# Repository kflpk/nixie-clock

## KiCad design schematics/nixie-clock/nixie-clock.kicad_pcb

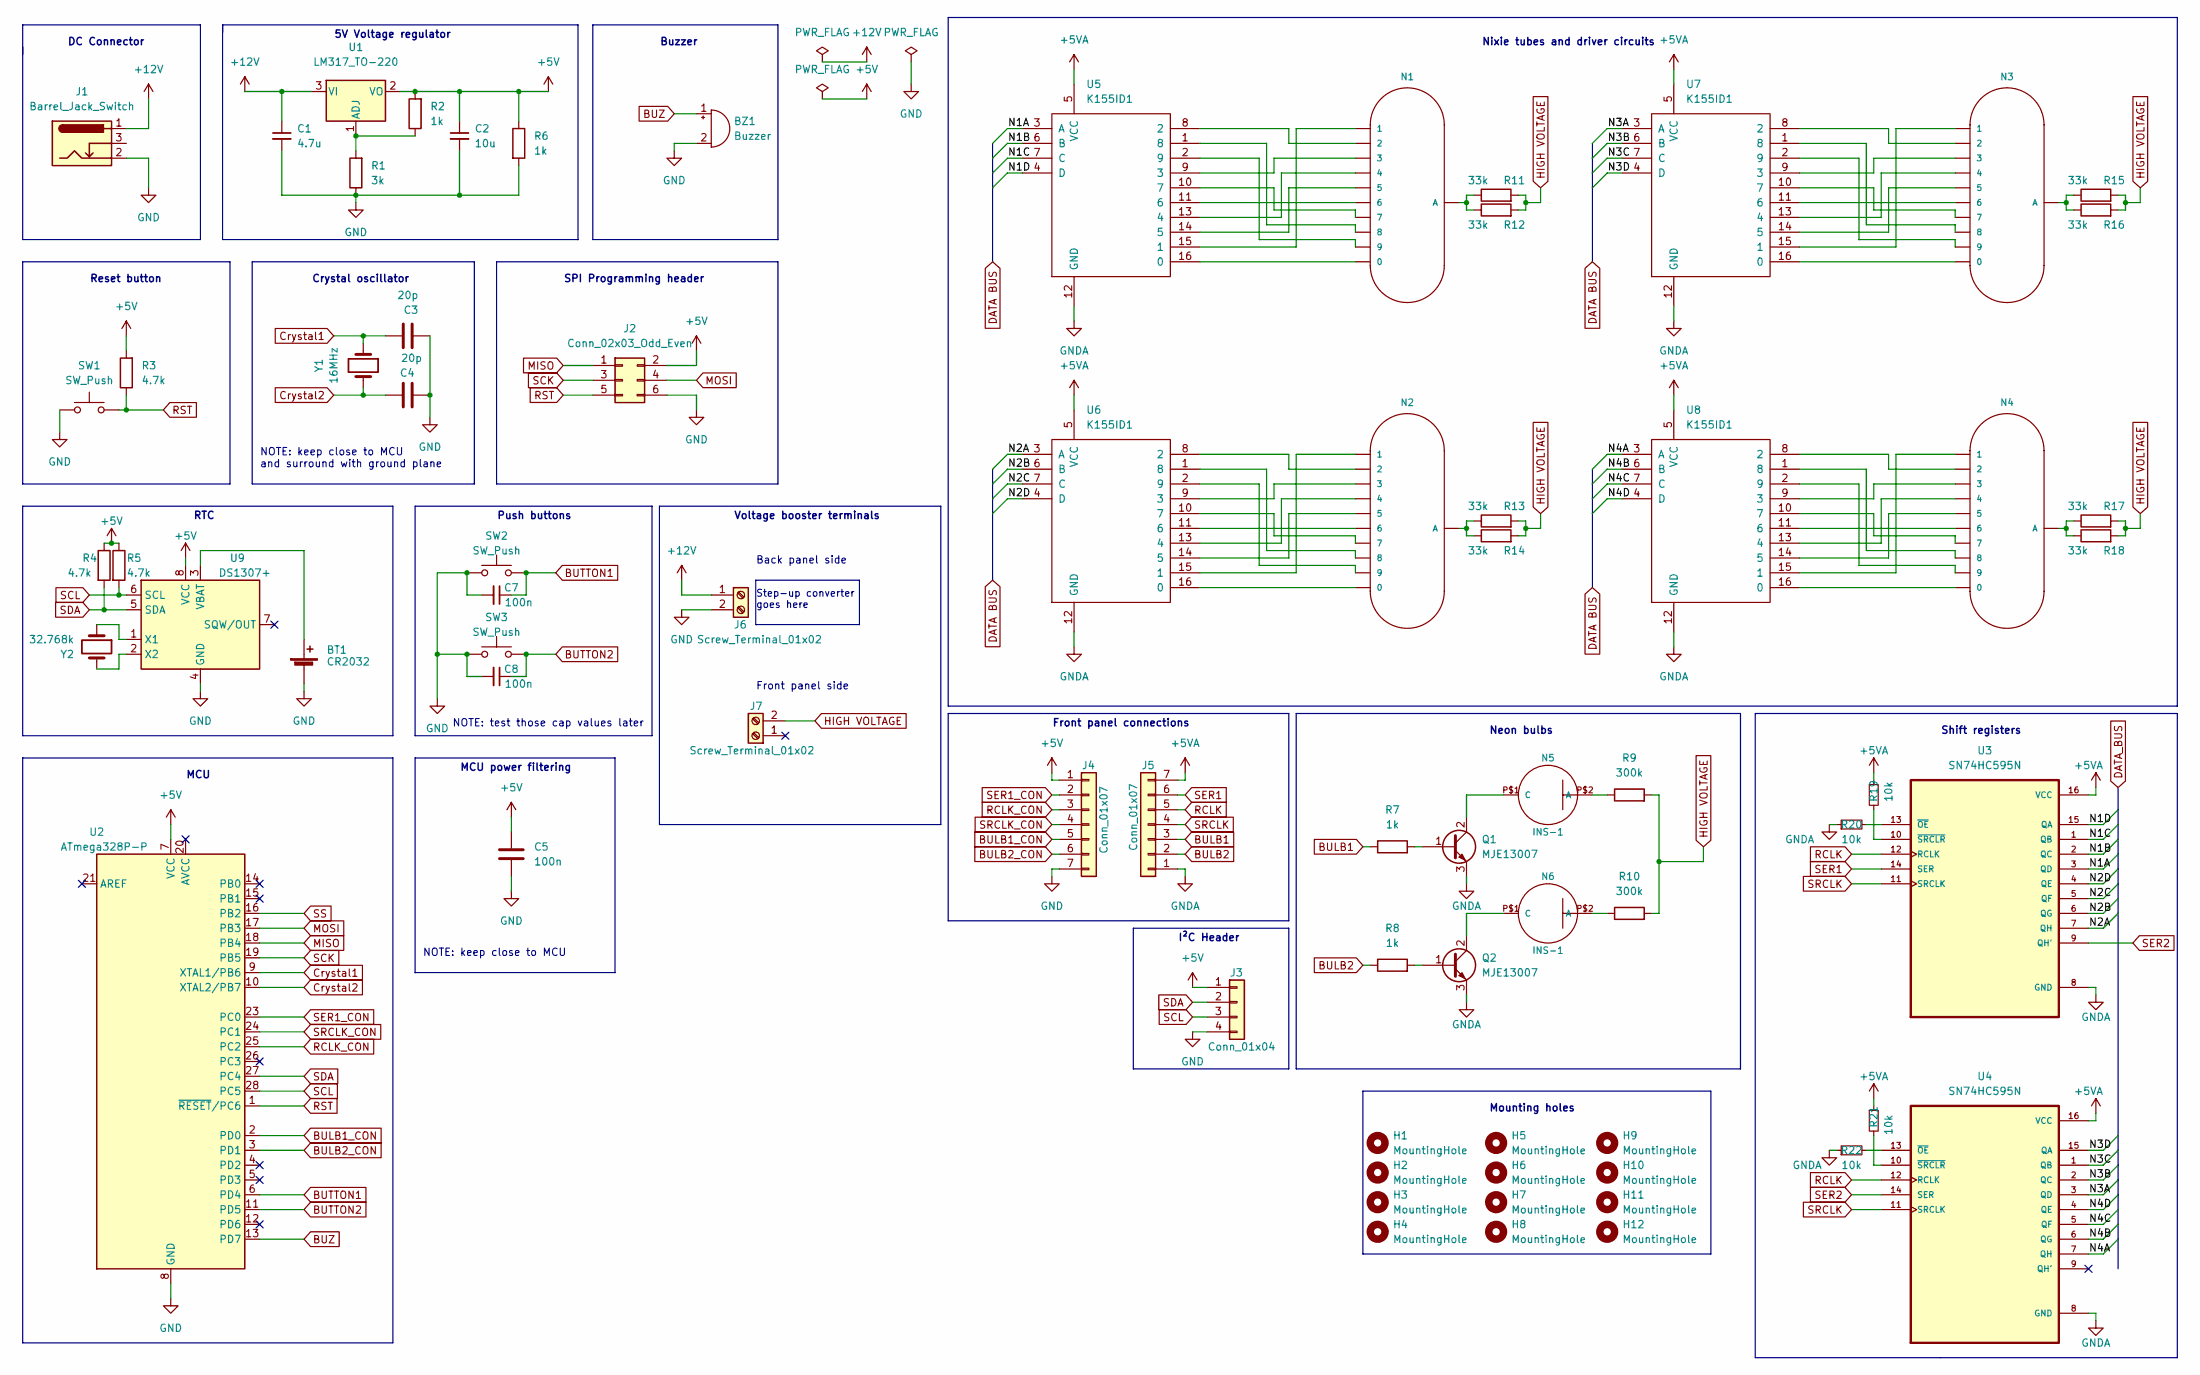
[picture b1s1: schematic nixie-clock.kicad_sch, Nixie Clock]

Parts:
BT1: CR2032; BatteryHolder_Keystone_1060_1x2032
BZ1: Buzzer; Buzzer_12x9.5RM7.6
C1: 4.7u; C_0805_2012Metric_Pad1.18x1.45mm_HandSolder
C2: 10u; C_0805_2012Metric_Pad1.18x1.45mm_HandSolder
C3, C4: 20p; C_0603_1608Metric_Pad1.08x0.95mm_HandSolder
C5, C7, C8: 100n; C_0805_2012Metric_Pad1.18x1.45mm_HandSolder
H1, H2, H3, H4, H5, H6, H7, H8, H9, H10, H11, H12: MountingHole; MountingHole_3mm
J1: Barrel_Jack_Switch; BarrelJack_Wuerth_6941xx301002
J2: Conn_02x03_Odd_Even; PinHeader_2x03_P2.54mm_Vertical
J3: Conn_01x04; PinHeader_1x04_P2.54mm_Vertical
J4, J5: Conn_01x07; PinHeader_1x07_P2.54mm_Horizontal
J6, J7: Screw_Terminal_01x02; TerminalBlock_Phoenix_MKDS-1,5-2_1x02_P5.00mm_Horizontal
N1, N2, N3, N4: IN-1
N5, N6: INS-1; mynixies-INS-1
Q1, Q2: MJE13007; TO-220-3_Vertical
R1: 3k; R_0805_2012Metric_Pad1.20x1.40mm_HandSolder
R2, R6, R7, R8: 1k; R_0805_2012Metric_Pad1.20x1.40mm_HandSolder
R3, R4, R5: 4.7k; R_0805_2012Metric_Pad1.20x1.40mm_HandSolder
R9, R10: 300k; R_0805_2012Metric_Pad1.20x1.40mm_HandSolder
R11, R12, R13, R14, R15, R16, R17, R18: 33k; R_1206_3216Metric_Pad1.30x1.75mm_HandSolder
R19, R20, R21, R22: 10k; R_0805_2012Metric_Pad1.20x1.40mm_HandSolder
SW1, SW2, SW3: SW_Push; SW_PUSH_6mm_H13mm
U1: LM317_TO-220; TO-220-3_Vertical
U2: ATmega328P-P; DIP-28_W7.62mm
U3, U4: SN74HC595N; DIP794W45P254L1969H508Q16
U5, U6, U7, U8: K155ID1; DIP-16_W7.62mm_Socket
U9: DS1307+; DIP-8_W7.62mm
Y1: 16MHz; Crystal_HC49-U_Vertical
Y2: 32.768k; Crystal_DS26_D2.0mm_L6.0mm_Horizontal

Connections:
+5V: C2.1, C5.1, J2.2, J3.1, J4.1, R2.2, R3.2, R4.1, R5.1, R6.1, U1.2 (VO), U2.7 (VCC), U9.8 (VCC)
+5VA: J5.7, R19.1, R21.1, U3.16 (VCC), U4.16 (VCC), U5.5 (VCC), U6.5 (VCC), U7.5 (VCC), U8.5 (VCC)
+12V: C1.1, J1.1, J6.1, U1.3 (VI)
/N1A: U3.3 (QD), U5.3 (A)
/N1B: U3.2 (QC), U5.6 (B)
/N1C: U3.1 (QB), U5.7 (C)
/N1D: U3.15 (QA), U5.4 (D)
/N2A: U3.7 (QH), U6.3 (A)
/N2B: U3.6 (QG), U6.6 (B)
/N2C: U3.5 (QF), U6.7 (C)
/N2D: U3.4 (QE), U6.4 (D)
/N3A: U4.3 (QD), U7.3 (A)
/N3B: U4.2 (QC), U7.6 (B)
/N3C: U4.1 (QB), U7.7 (C)
/N3D: U4.15 (QA), U7.4 (D)
/N4A: U4.7 (QH), U8.3 (A)
/N4B: U4.6 (QG), U8.6 (B)
/N4C: U4.5 (QF), U8.7 (C)
/N4D: U4.4 (QE), U8.4 (D)
BULB1: J5.3, R7.1
BULB1_CON: J4.5, U2.2 (PD0)
BULB2: J5.2, R8.1
BULB2_CON: J4.6, U2.3 (PD1)
BUTTON1: C7.1, SW2.2, U2.6 (PD4)
BUTTON2: C8.1, SW3.2, U2.11 (PD5)
BUZ: BZ1.1 (-), U2.13 (PD7)
Crystal1: C3.2, U2.9 (XTAL1/PB6), Y1.1
Crystal2: C4.2, U2.10 (XTAL2/PB7), Y1.2
GND: BT1.2 (-), BZ1.2 (+), C1.2, C2.2, C3.1, C4.1, C5.2, C7.2, C8.2, J1.2, J2.6, J3.4, J4.7, J6.2, R1.1, R6.2, SW1.1, SW2.1, SW3.1, U2.8 (GND), U2.22 (GND), U9.4 (GND)
GNDA: J5.1, Q1.3 (E), Q2.3 (E), R20.1, R22.1, U3.8 (GND), U4.8 (GND), U5.12 (GND), U6.12 (GND), U7.12 (GND), U8.12 (GND)
HIGH VOLTAGE: J7.2, R9.2, R10.2, R11.2, R12.2, R13.2, R14.2, R15.2, R16.2, R17.2, R18.2
MISO: J2.1, U2.18 (PB4)
MOSI: J2.4, U2.17 (PB3)
unnamed: BT1.1 (+), U9.3 (VBAT)
unnamed: N1.0, U5.16 (0)
unnamed: N1.1, U5.15 (1)
unnamed: N1.2, U5.8 (2)
unnamed: N1.3, U5.9 (3)
unnamed: N1.4, U5.13 (4)
unnamed: N1.5, U5.14 (5)
unnamed: N1.6, U5.11 (6)
unnamed: N1.7, U5.10 (7)
unnamed: N1.8, U5.1 (8)
unnamed: N1.9, U5.2 (9)
unnamed: N1.A, R11.1, R12.1
unnamed: N2.0, U6.16 (0)
unnamed: N2.1, U6.15 (1)
unnamed: N2.2, U6.8 (2)
unnamed: N2.3, U6.9 (3)
unnamed: N2.4, U6.13 (4)
unnamed: N2.5, U6.14 (5)
unnamed: N2.6, U6.11 (6)
unnamed: N2.7, U6.10 (7)
unnamed: N2.8, U6.1 (8)
unnamed: N2.9, U6.2 (9)
unnamed: N2.A, R13.1, R14.1
unnamed: N3.0, U7.16 (0)
unnamed: N3.1, U7.15 (1)
unnamed: N3.2, U7.8 (2)
unnamed: N3.3, U7.9 (3)
unnamed: N3.4, U7.13 (4)
unnamed: N3.5, U7.14 (5)
unnamed: N3.6, U7.11 (6)
unnamed: N3.7, U7.10 (7)
unnamed: N3.8, U7.1 (8)
unnamed: N3.9, U7.2 (9)
unnamed: N3.A, R15.1, R16.1
unnamed: N4.0, U8.16 (0)
unnamed: N4.1, U8.15 (1)
unnamed: N4.2, U8.8 (2)
unnamed: N4.3, U8.9 (3)
unnamed: N4.4, U8.13 (4)
unnamed: N4.5, U8.14 (5)
unnamed: N4.6, U8.11 (6)
unnamed: N4.7, U8.10 (7)
unnamed: N4.8, U8.1 (8)
unnamed: N4.9, U8.2 (9)
unnamed: N4.A, R17.1, R18.1
unnamed: N5.P$1 (C), Q1.2 (C)
unnamed: N5.P$2 (A), R9.1
unnamed: N6.P$1 (C), Q2.2 (C)
unnamed: N6.P$2 (A), R10.1
unnamed: Q1.1 (B), R7.2
unnamed: Q2.1 (B), R8.2
unnamed: R1.2, R2.1, U1.1 (ADJ)
unnamed: R19.2, U3.10 (~SRCLR)
unnamed: R20.2, U3.13 (~OE)
unnamed: R21.2, U4.10 (~SRCLR)
unnamed: R22.2, U4.13 (~OE)
unnamed: U9.1 (X1), Y2.1
unnamed: U9.2 (X2), Y2.2
RCLK: J5.5, U3.12 (RCLK), U4.12 (RCLK)
RCLK_CON: J4.3, U2.25 (PC2)
RST: J2.5, R3.1, SW1.2, U2.1 (~RESET/PC6)
SCK: J2.3, U2.19 (PB5)
SCL: J3.3, R5.2, U2.28 (PC5), U9.6 (SCL)
SDA: J3.2, R4.2, U2.27 (PC4), U9.5 (SDA)
SER1: J5.6, U3.14 (SER)
SER1_CON: J4.2, U2.23 (PC0)
SER2: U3.9 (QH'), U4.14 (SER)
SRCLK: J5.4, U3.11 (SRCLK), U4.11 (SRCLK)
SRCLK_CON: J4.4, U2.24 (PC1)
SS: U2.16 (PB2)

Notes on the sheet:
Step-up converter goes here
DC Connector
Nixie tubes and driver circuits
I²C Header
SPI Programming header
MCU power filtering
NOTE: keep close to MCU
Crystal oscillator
MCU
NOTE: test those cap values later
5V Voltage regulator
Buzzer
Front panel connections
Front panel side
RTC
Push buttons
Voltage booster terminals
Back panel side
NOTE: keep close to MCU and surround with ground plane
Neon bulbs
Shift registers
Reset button
Mounting holes

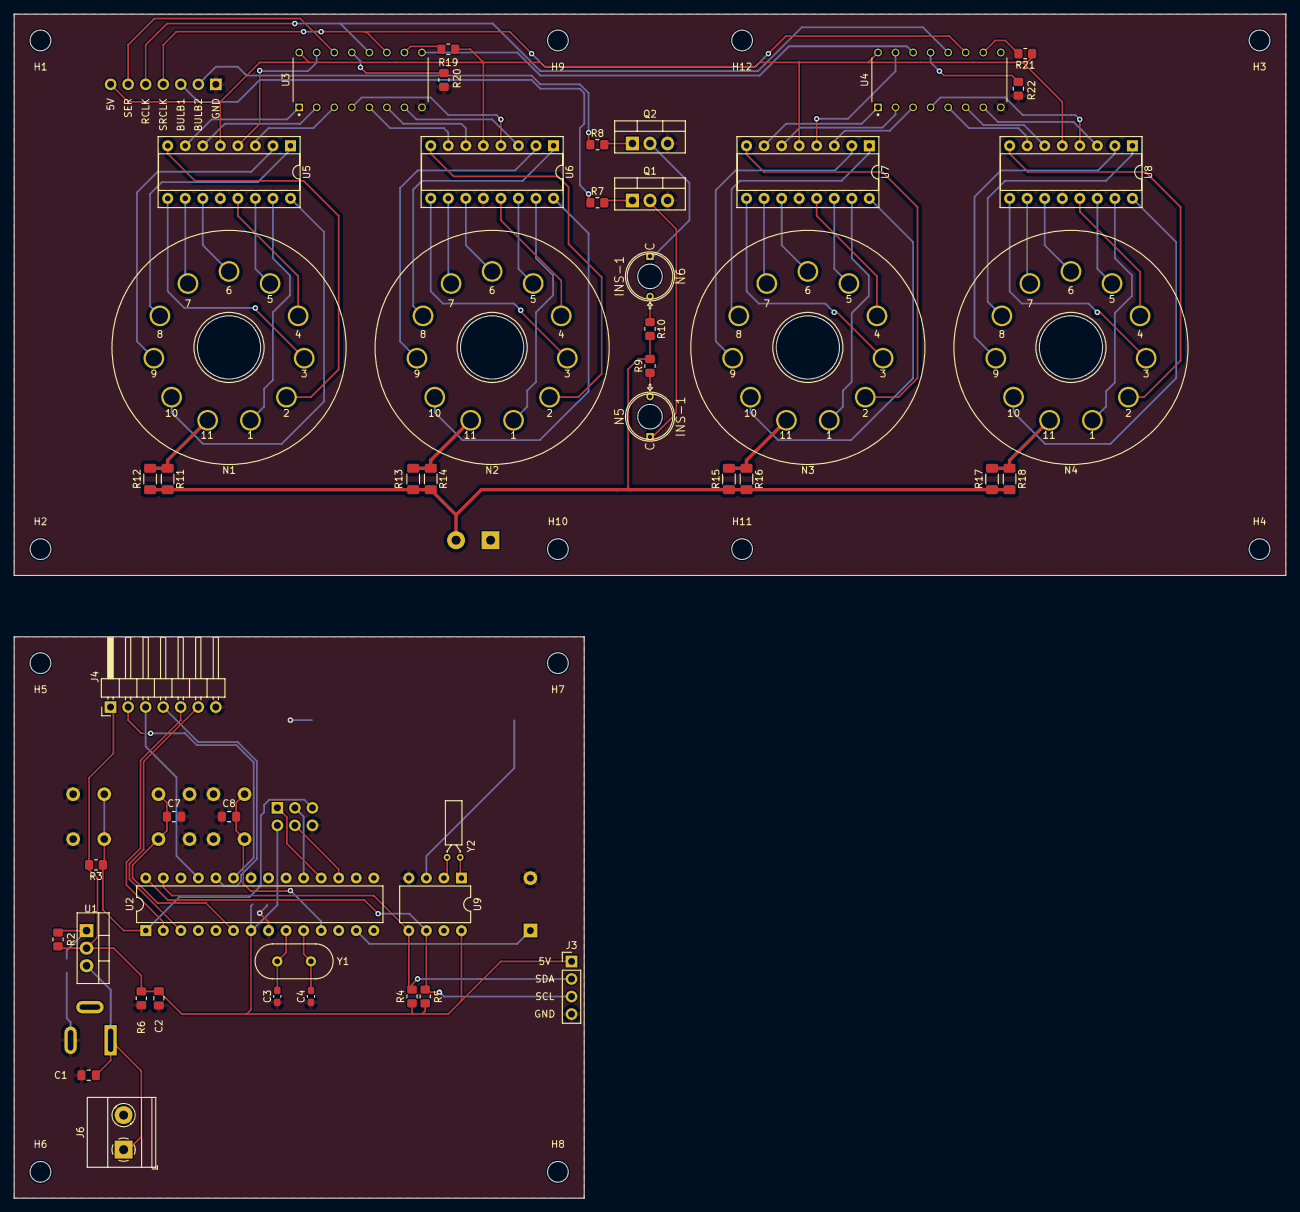
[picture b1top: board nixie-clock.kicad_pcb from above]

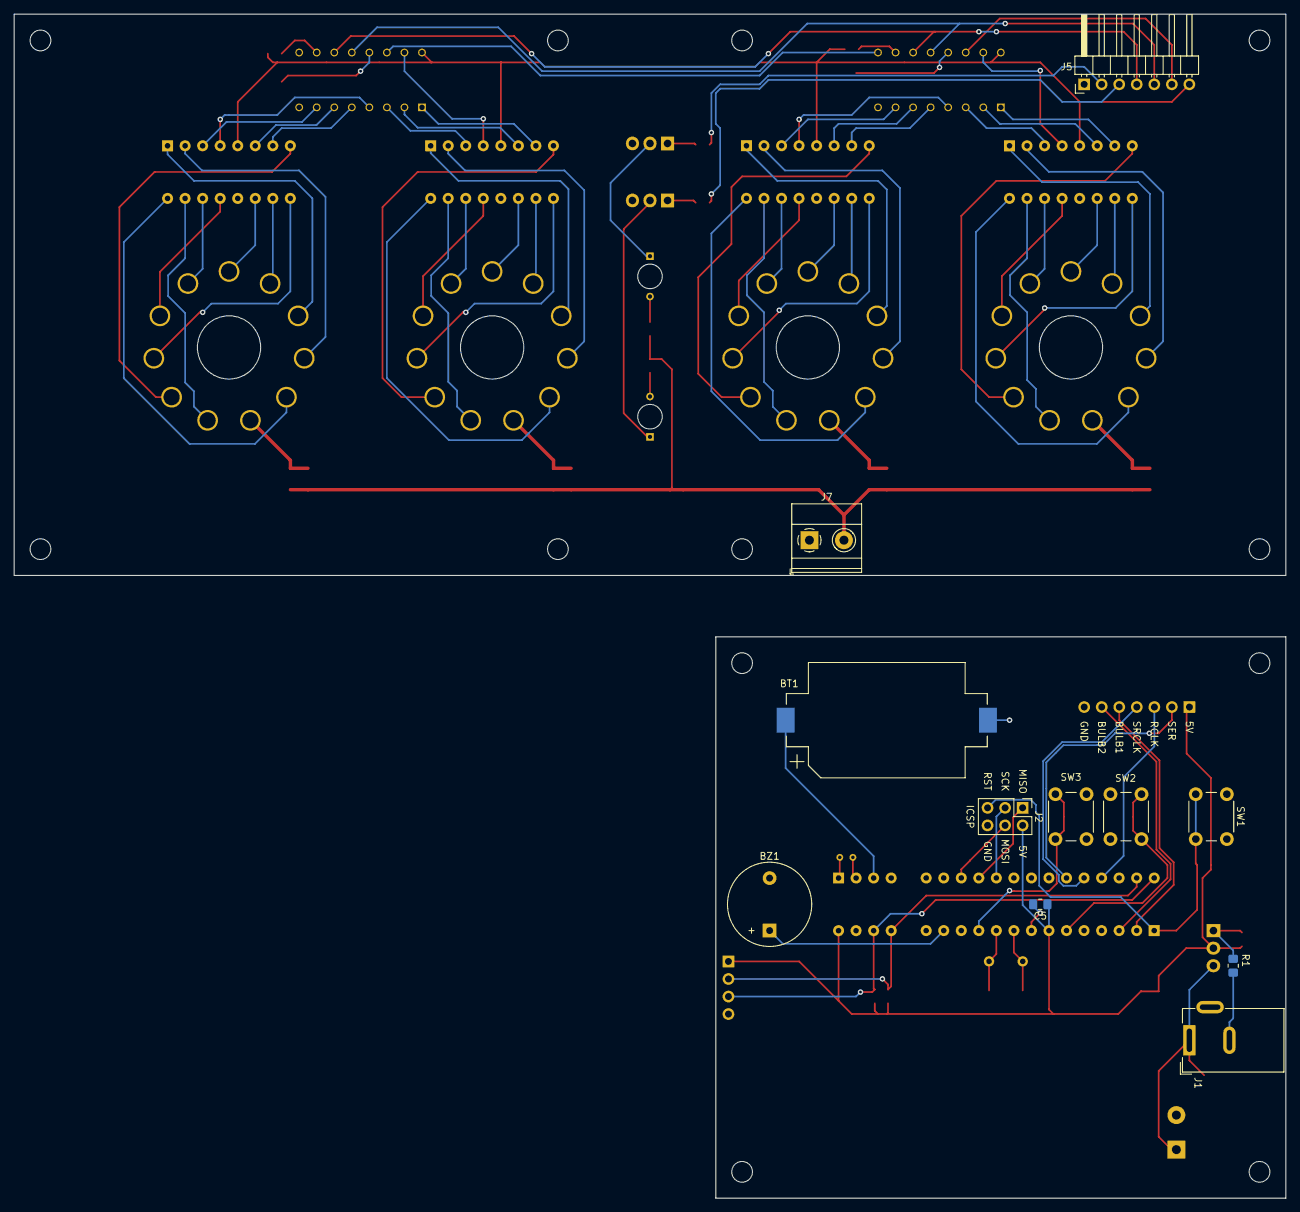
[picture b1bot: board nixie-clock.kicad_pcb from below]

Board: 2 copper layers, 184.1 x 171.4 mm, 72 parts (11 on the bottom side), 102 nets.

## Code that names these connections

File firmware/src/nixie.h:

#ifndef NIXIE_H
#define NIXIE_H

#include <inttypes.h>
#include <avr/io.h>
#include <util/delay.h>

#define SER_PORT   PORTC
#define SER_PIN    PC0

#define SRCLK_PORT PORTC
#define SRCLK_PIN  PC1

#define RCLK_PORT  PORTC
#define RCLK_PIN   PC2

void display_init();
void display_numbers(uint8_t num1, uint8_t num2, 
                     uint8_t num3, uint8_t num4);
void push_number(uint8_t number);
void refresh_display(void);

#endif

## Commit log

2023-03-16 started to make the schematic
2023-03-17 annotated nixie driver's inputs
2023-03-17 added dependencies as submodules
2023-03-19 schematic: added buttons, rtc, neon bulbs, annotated driver input labels
2023-03-19 footprints: added basic IN-1 footprint, requires further corrections
2023-03-25 schematic: corrected k155id1's pinout to dip16 instead of 14
2023-03-25 schematic: added in-1 footprint from included library
2023-03-26 annotated components, added footprints to most caps and ICs
2023-03-27 schematic: added transistor model
2023-03-27 schematic: assigned all footprints, schematic finished (i hope)
2023-03-27 schematic: added mounting holes
2023-03-28 schematics: asigned footprints, started working on PCB, modified in-1 footprint
2023-03-28 schematic correction: added anode resistors for nixie tubes
2023-04-04 annotated some more components idk
2023-04-05 schematic: added inter-panel connection
2023-04-05 schematic: corrected connectors, separated front and back panel power pins
2023-04-05 pcb: placed elements on main board, added mounting holes
2023-04-06 pcb: finished, tweaks to be done
2023-04-06 pcb: updated in-1 footprint, so the center hole now works in main PCB
2023-04-06 footprints: removed edge cuts from in-1 footprint
2023-04-06 pcb: pushed back angled goldpin headers, updated in-1 footprints on pcb
2023-04-16 fimrware: started doing ds1308 api
2023-04-17 working makefile, addressing devices on i2c bus works, reading and writing to be done
2023-04-17 minor changes to makefile
2023-04-17 firmware: two wire library sending and receiving works
2023-04-17 firmware: added buffer read and write, and prototypes for ds1307 functions
2023-04-20 added time-getting and time-setting functions
2023-04-20 error correction in DS_get_time
2023-04-24 added reset to nixie init
2023-04-25 simple test of the display
2023-04-26 schematic correction: active low OE on shift regs is now connected correctly; added pullup and pulldown resistors to shift reg
2023-04-26 pcb: updated pcb according to the schematic, added silkscreen for headers
2023-05-07 twi: added timeouts, replaced TWSR codes with macros
2023-05-12 dump
